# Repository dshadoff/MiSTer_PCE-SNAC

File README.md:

# MiSTer_PCE-SNAC converter board

This is a board designed to work with the MiSTer FPGA system, and is originally based on
the SNAC designs from blue212 at https://github.com/blue212/SNAC

The PC Engine controller system has higher-speed requirements than most other systems, and
as a result, the regular open-collector SNAC boards don't really work for most situations
(ie. auto-fire, 6-button controller, turbotap, PCE mouse, Memory Base 128, etc.).  This is
because the rise time on the pulses is not fast enough among other things.  This board
was designed to address these issues.

While designing it, I also felt that I wanted as small a board as possible, so I decided
to integrate the regular "surfboard" SNAC and the adapter, integrating them into a single
device.  I also shrunk all the components as much as possible, and chose easily-obtainable
parts so that I could get them assembled by JLCPCB's SMT assembly service at a very good
price.  (However they don't mount connectors.)

I designed the board using the free version of EAGLE (2-layer, less than 100mm on both
X- and Y-axes).  The gerbers are included in this repository, including the files required
by JLCPCB's SMT assembly forms, in case you want to get your own set made.

The board measures 37mm x 22mm (plus USB plug).  Here is a picture:

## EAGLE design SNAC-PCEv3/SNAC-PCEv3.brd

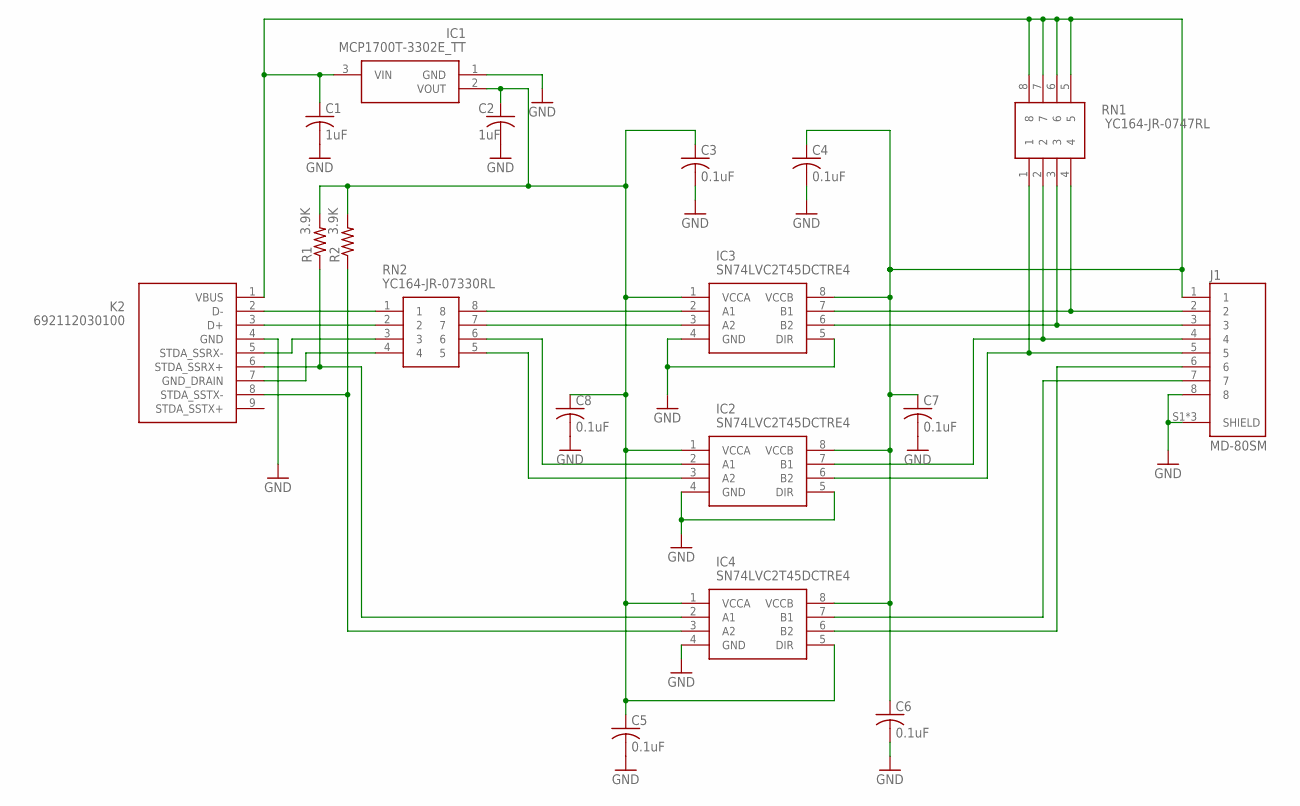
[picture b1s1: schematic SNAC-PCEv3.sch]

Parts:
C1, C2: 1uF; C0603
C3, C4, C5, C6, C7, C8: 0.1uF; C0402
IC1: MCP1700T-3302E_TT; SOT95P237X112-3N
IC2, IC3, IC4: SN74LVC2T45DCTRE4; SOP65P400X130-8N
J1: MD-80SM; CUI_MD-80SM
K2: 692112030100; MPN TXS0108EPWR
R1, R2: 3.9K; R0402
RN1: YC164-JR-0747RL; YC164JR07220RL
RN2: YC164-JR-07330RL; YC164JR07220RL

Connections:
3V3: C2.1, C3.1, C5.1, C8.1, IC1.2 (VOUT), IC2.1 (VCCA), IC3.1 (VCCA), IC4.1 (VCCA), IC4.5 (DIR), R1.2, R2.2
5V: C1.1, C4.1, C6.1, C7.1, IC1.3 (VIN), IC2.8 (VCCB), IC3.8 (VCCB), IC4.8 (VCCB), J1.1, K2.1 (VBUS), RN1.5, RN1.6, RN1.7, RN1.8
GND: C1.2, C2.2, C3.2, C4.2, C5.2, C6.2, C7.2, C8.2, IC1.1 (GND), IC2.4 (GND), IC2.5 (DIR), IC3.4 (GND), IC3.5 (DIR), IC4.4 (GND), J1.8, J1.S1 (SHIELD), J1.S2 (SHIELD), J1.S3 (SHIELD), K2.4 (GND)
unnamed: K2.2 (D-), RN2.1
unnamed: IC3.7 (B1), J1.2, RN1.4
unnamed: IC3.3 (A2), RN2.7
unnamed: IC2.7 (B1), J1.4, RN1.2
unnamed: IC3.2 (A1), RN2.8
unnamed: K2.3 (D+), RN2.2
unnamed: K2.5 (STDA_SSRX-), RN2.3
unnamed: IC4.7 (B1), J1.7
unnamed: IC3.6 (B2), J1.3, RN1.3
unnamed: IC2.6 (B2), J1.5, RN1.1
unnamed: IC4.6 (B2), J1.6
unnamed: IC2.2 (A1), RN2.6
unnamed: K2.7 (GND_DRAIN), RN2.4
unnamed: IC2.3 (A2), RN2.5
RX+: IC4.2 (A1), K2.6 (STDA_SSRX+), R1.1
TX-: IC4.3 (A2), K2.8 (STDA_SSTX-), R2.1

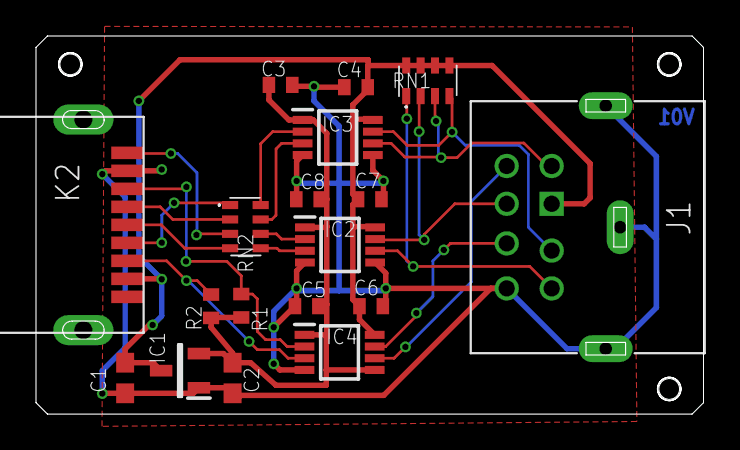
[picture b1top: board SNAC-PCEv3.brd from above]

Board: 2 copper layers, 37.1 x 21.0 mm, 18 parts (0 on the bottom side), 19 nets.

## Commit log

2020-07-07 Add picture
2020-07-07 Minor edits

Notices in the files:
parts and their libraries:
Wuerth_Elektronik_eiCan_Communication_Co: Copyright: Würth Elektronik
